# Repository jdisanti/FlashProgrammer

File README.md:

128KiB 17-bit Addressed 32-pin Flash ROM Programmer
---------------------------------------------------

This package includes the schematic, PCB design, and software for an USB
Flash Programmer to read/write the contents of 128KiB 32-pin Flash ROM chips,
such as the GLS27SF010 by Greenliant.

This is my second electronics project, and a stepping stone to building my
own 8-bit computer. I made a lot of mistakes along the way and learned a ton.
After four PCB revisions, and hours of frustrating debugging, I finally got it
to successfully erase, write, and verify the contents of a ROM.

## Demo

## Project Structure

The `avr/` directory contains all of the software to be run on the Atmel
ATMEGA328 chip on the board. This needs to be compiled and programmed onto
the board using an ISP on the ISP headers.

The `design/` directory contains the schematic and PCB design in the original
KiCad file formats. The BOM file is also here.

The `PDFs/` directory contains PDF output for the schematic and PCB.

The `software/` directory contains the software that runs on the PC to
communicate with the device over USB serial. It's written in Rust and can
be compiled/run on Linux, Mac, and Windows without a hitch.

Finally, `symbol_generation/` contains some CSV files used to generate
schematic symbols with KiPart.

## What I Learned

This project presented a lot of firsts for me. My previous project, a binary
clock, had taught me how to design a digital circuit with a microcontroller,
draw schematics, and create PCBs.

This project, above all other things, taught me patience. If you read the
next section about the mistakes I made, you'll see why. I learned that I
really need to slow down, be sure to read all of the datasheets, double
check my schematics and footprints, and cross-check my schematic against
the datasheets. Then after all of that, wait a week and then do it again.

Coming from a software background made this a very hard lesson. I'm used to
making small incremental changes and getting test results immediately. Working
in an area where incremental changes are expensive, and where testing is
time-consuming, requires a difficult change of mindset.

Something I didn't do with this project was breadboarding. I wanted to see
if I could design and build a working circuit without that step. I've learned
that I can play around with little "mock" circuits in LTSpice to test some
of my assumptions, and then also build those out on breadboard without having
to build the entire circuit. This was useful for designing the A9 signal/12V
switching circuit.

## Mistakes I Made

Since the goal of this project was to learn, I've decided to document all
the mistakes I made for future reference.

**First board (not in version control)**
- I didn't read the entire datasheet for the MAX662A, and thus, didn't realize
  I needed capacitors on the 12V output. This led to there being no 12V supply
  on that board.
- I tried to be clever and soldered the board up in sections so I could test each
  individually. This is how I discovered the 12V supply wasn't working, but I didn't
  continue testing the other sections after that discovery, and thus, didn't
  discover my next mistake until the next board.

**Second board**
- I got the pins on the SOT-23 2N3906 transistor wrong, and lost a decent
  chunk of time debugging that, and then soldering it on upside-down to fix it.
- I discovered that I couldn't use the daisy chaining pin on the 74HC595
  as the 17th bit of the address. I should have looked at the timing diagram
  in the datasheet to verify my assumption. I was actually able to bodge this
  by severing the A16 line and wiring it to the three unused pins on the micro
  (and setting all three pins to the same output since they were tied together).
- I used the ISP pins for both programming the MCU and talking to the ROM chip,
  but I neglected to add resistors so that I could program the MCU while the
  ROM chip was populated on the board. Unfortunately, I didn't realize this at
  the time, and thought I had fried my MCU somehow. Since I had already discovered
  the address line mistake, I just built another revision instead of doing
  more testing (I didn't have a rework station at the time and didn't want to
  solder another board either).

**Third board**
- I discovered that erasing didn't work because I failed to realize that
  the 12V had to be applied to both the VPP and A9 pins during the erase process.

**Fourth board**
- I didn't put a pull-down resistor on the A9 signal after the diodes. This
  forced me to add a hefty delay loop of 160uS in the code that set the address.
  This mistake is still present in the design since it wasn't fatal.

## License

All of the contents of this package are licensed under the Solderpad 0.51
license. Please read the LICENSE.md included for more details.

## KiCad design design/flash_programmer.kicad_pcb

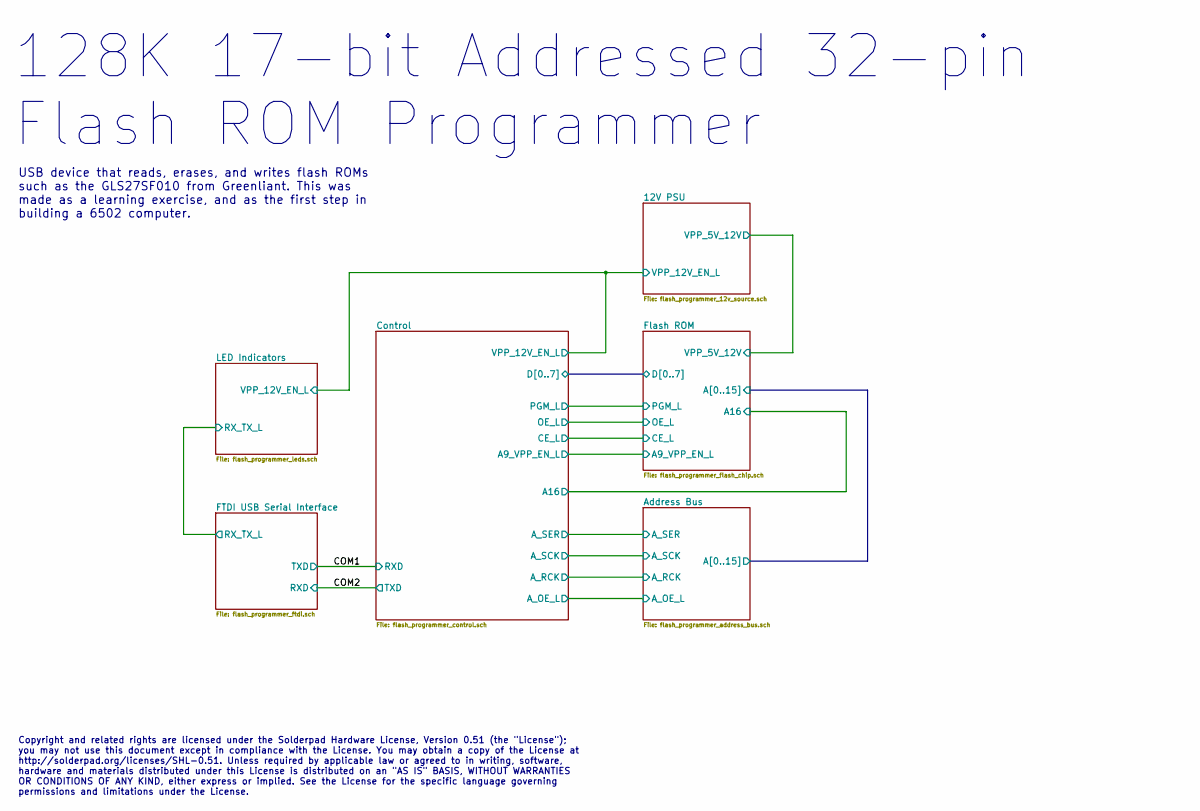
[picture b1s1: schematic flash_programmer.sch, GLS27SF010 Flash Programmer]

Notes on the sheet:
128K 17-bit Addressed 32-pin Flash ROM Programmer
USB device that reads, erases, and writes flash ROMs such as the GLS27SF010 from Greenliant. This was made as a learning exercise, and as the first step in building a 6502 computer.
Copyright and related rights are licensed under the Solderpad Hardware License, Version 0.51 (the "License"); you may not use this document except in compliance with the License. You may obtain a copy of the License at http://solderpad.org/licenses/SHL-0.51. Unless required by applicable law or agr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

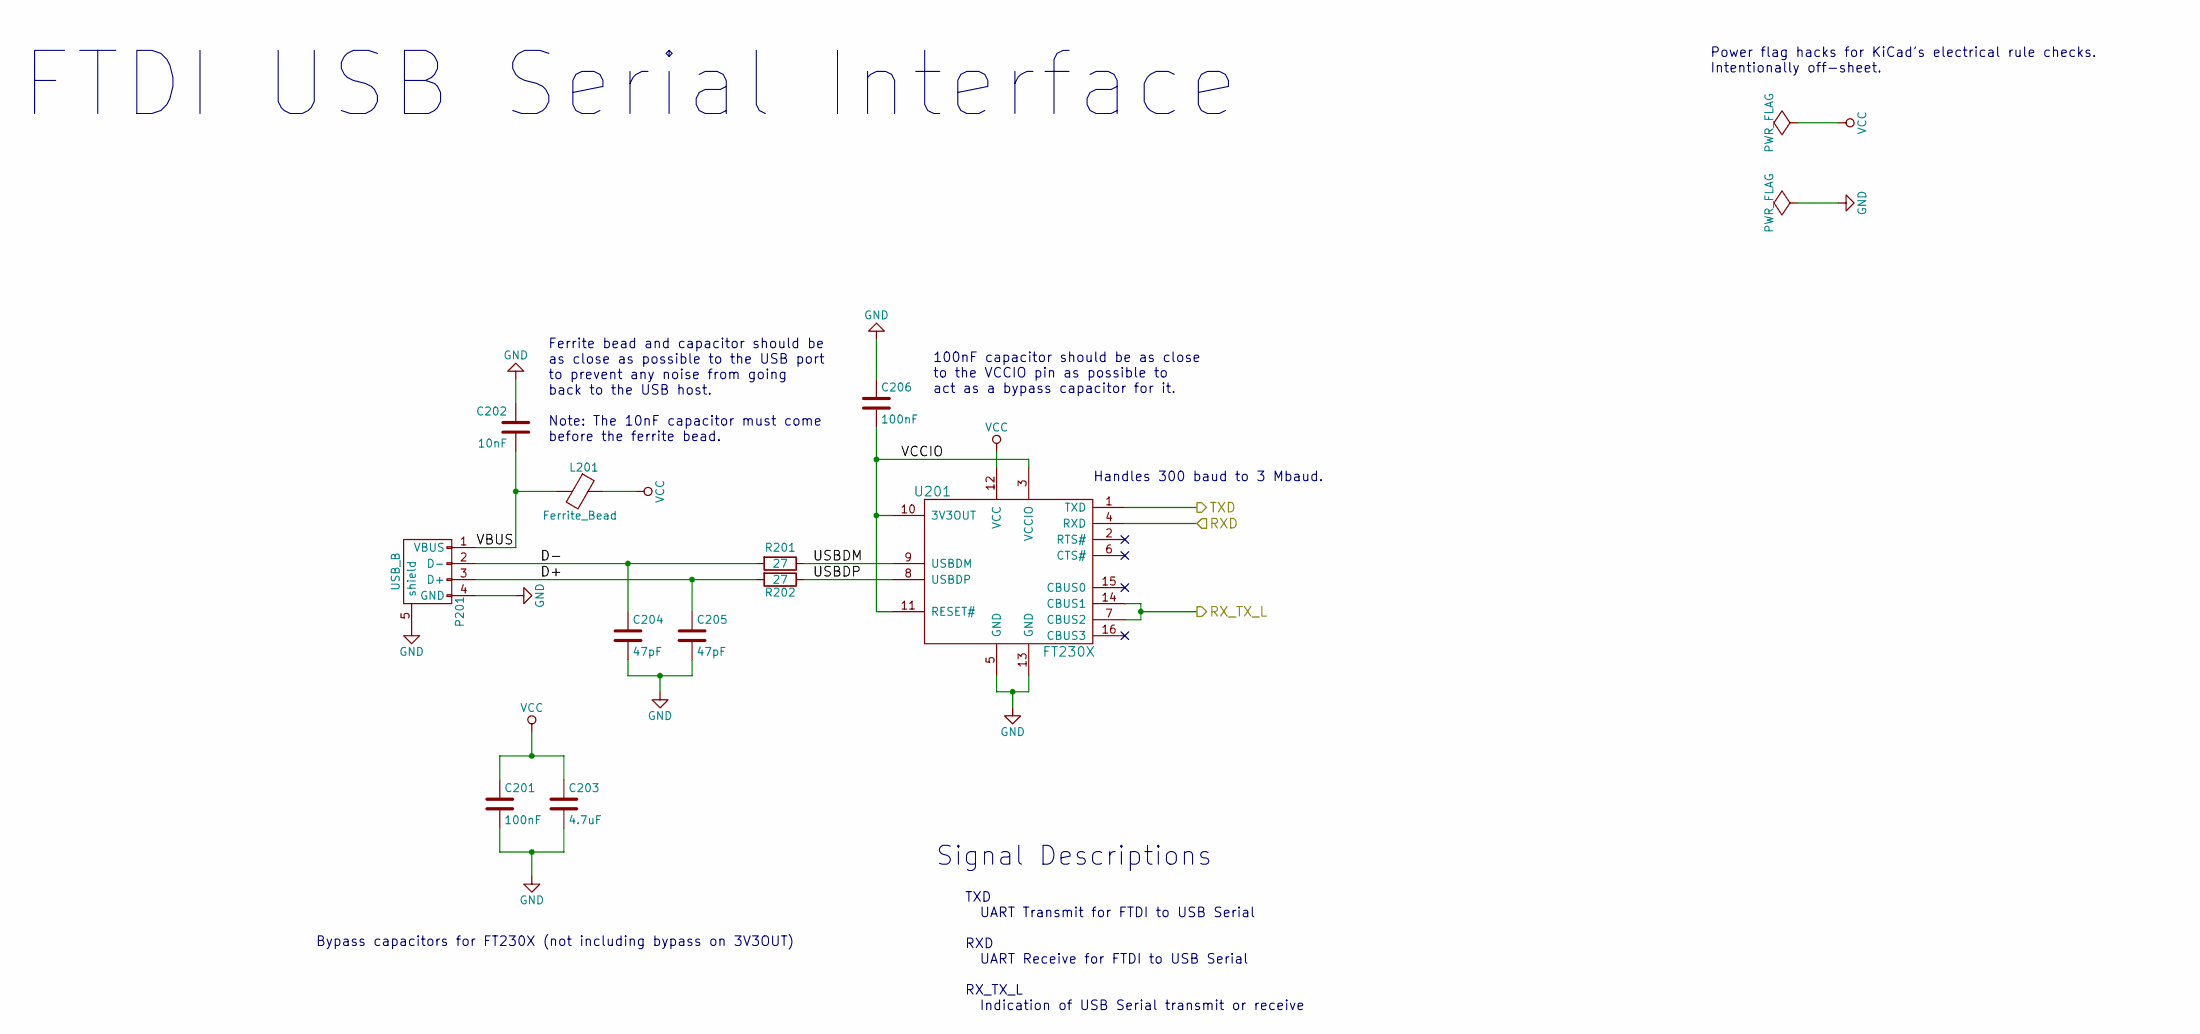
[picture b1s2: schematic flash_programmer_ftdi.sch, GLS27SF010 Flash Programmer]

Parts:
C201, C206: 100nF; R_0603_HandSoldering
C202: 10nF; R_0603_HandSoldering
C203: 4.7uF; R_0805_HandSoldering
C204, C205: 47pF; R_0603_HandSoldering
L201: Ferrite_Bead; R_0805_HandSoldering
P201: USB_B
R201, R202: 27; R_0603_HandSoldering
U201: FT230X; SSOP-16

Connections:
/COM1: U201.1 (TXD); also elsewhere on the board
/COM2: U201.4 (RXD); also elsewhere on the board
/FTDI USB Serial Interface/D+: C205.1, P201.3 (D+), R202.2
/FTDI USB Serial Interface/D-: C204.1, P201.2 (D-), R201.2
/FTDI USB Serial Interface/RX_TX_L: U201.7 (CBUS2), U201.14 (CBUS1); also elsewhere on the board
/FTDI USB Serial Interface/USBDM: R201.1, U201.9 (USBDM)
/FTDI USB Serial Interface/USBDP: R202.1, U201.8 (USBDP)
/FTDI USB Serial Interface/VBUS: C202.1, L201.2, P201.1 (VBUS)
/FTDI USB Serial Interface/VCCIO: C206.2, U201.3 (VCCIO), U201.10 (3V3OUT), U201.11 (RESET#)
GND: C201.2, C202.2, C203.2, C204.2, C205.2, C206.1, P201.4 (GND), P201.5 (shield), U201.5 (GND), U201.13 (GND); also elsewhere on the board
VCC: C201.1, C203.1, L201.1, U201.12 (VCC); also elsewhere on the board

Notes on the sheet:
Bypass capacitors for FT230X (not including bypass on 3V3OUT)
Ferrite bead and capacitor should be as close as possible to the USB port to prevent any noise from going back to the USB host. Note: The 10nF capacitor must come before the ferrite bead.
100nF capacitor should be as close to the VCCIO pin as possible to act as a bypass capacitor for it.
Power flag hacks for KiCad's electrical rule checks. Intentionally off-sheet.
FTDI USB Serial Interface
Signal Descriptions
TXD UART Transmit for FTDI to USB Serial RXD UART Receive for FTDI to USB Serial RX_TX_L Indication of USB Serial transmit or receive
Handles 300 baud to 3 Mbaud.

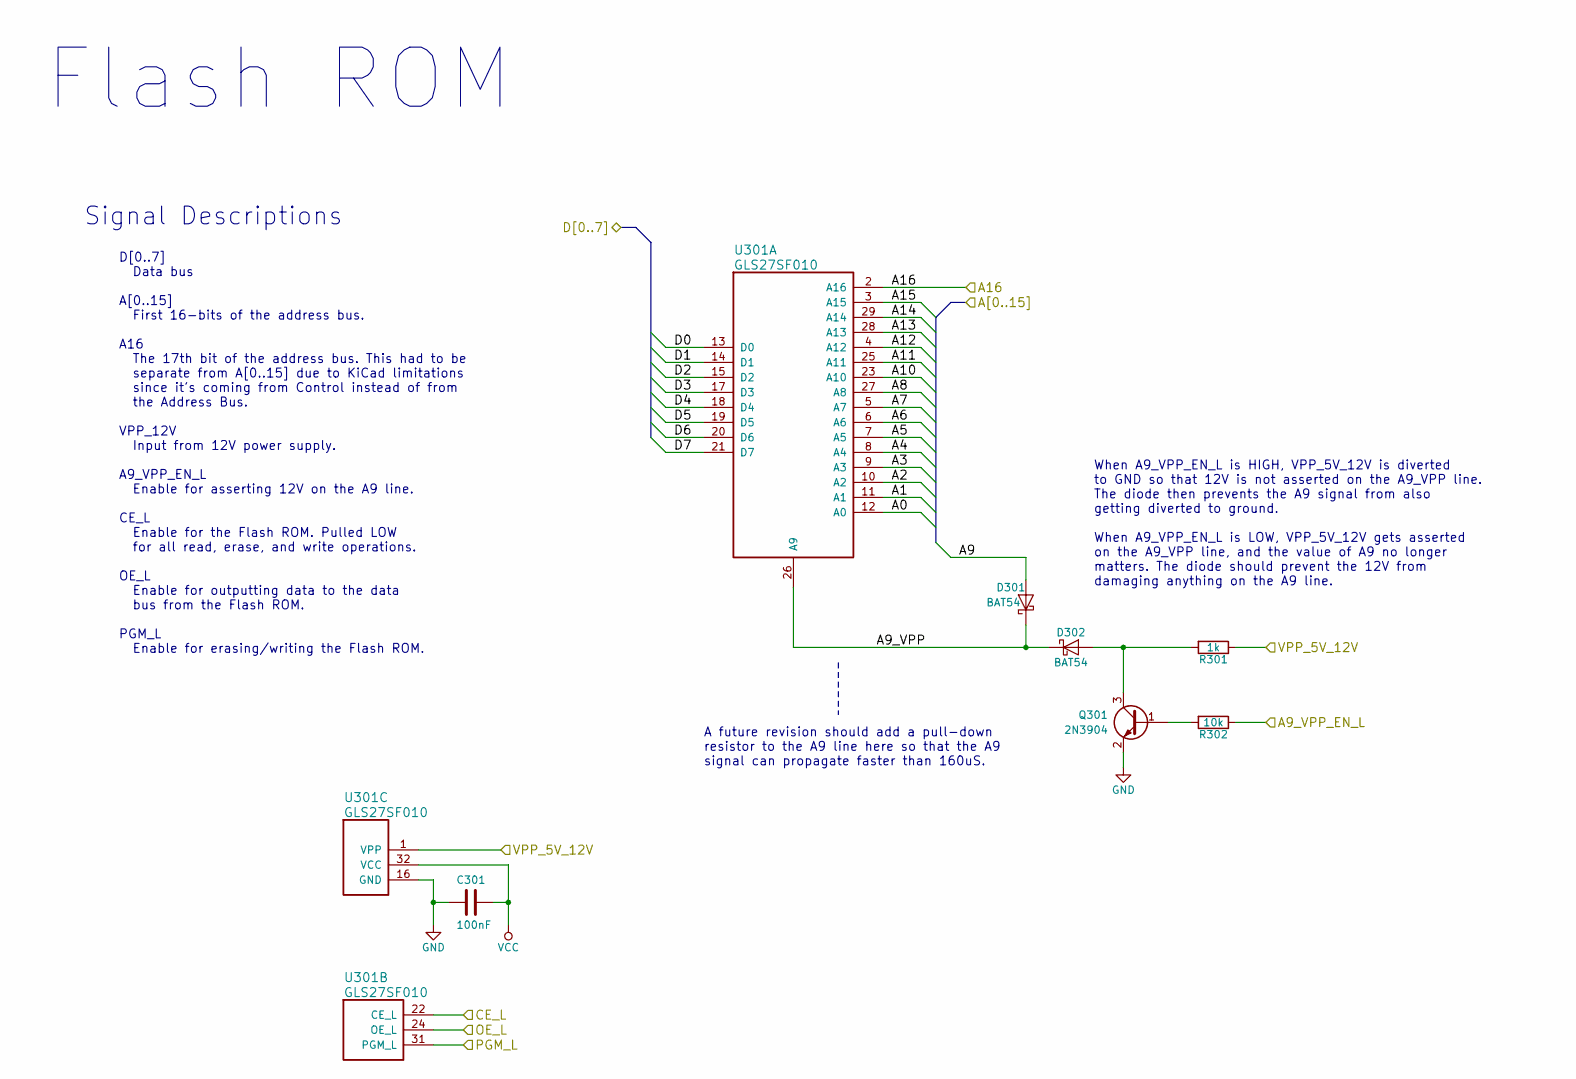
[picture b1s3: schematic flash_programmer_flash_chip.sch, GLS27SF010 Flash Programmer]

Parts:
C301: 100nF; R_0603_HandSoldering
D301, D302: BAT54; D_SOT-23_ANK
Q301: 2N3904; SOT-23_Handsoldering
R301: 1k; R_0603_HandSoldering
R302: 10k; R_0603_HandSoldering
U301: GLS27SF010; DIP-32_W15.24mm

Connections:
/12V PSU/VPP_5V_12V: R301.1, U301.1 (VPP); also elsewhere on the board
/Address Bus/A0: U301.12 (A0); also elsewhere on the board
/Address Bus/A1: U301.11 (A1); also elsewhere on the board
/Address Bus/A2: U301.10 (A2); also elsewhere on the board
/Address Bus/A3: U301.9 (A3); also elsewhere on the board
/Address Bus/A4: U301.8 (A4); also elsewhere on the board
/Address Bus/A5: U301.7 (A5); also elsewhere on the board
/Address Bus/A6: U301.6 (A6); also elsewhere on the board
/Address Bus/A7: U301.5 (A7); also elsewhere on the board
/Address Bus/A8: U301.27 (A8); also elsewhere on the board
/Address Bus/A9: D301.2 (A); also elsewhere on the board
/Address Bus/A10: U301.23 (A10); also elsewhere on the board
/Address Bus/A11: U301.25 (A11); also elsewhere on the board
/Address Bus/A12: U301.4 (A12); also elsewhere on the board
/Address Bus/A13: U301.28 (A13); also elsewhere on the board
/Address Bus/A14: U301.29 (A14); also elsewhere on the board
/Address Bus/A15: U301.3 (A15); also elsewhere on the board
/Control/A9_VPP_EN_L: R302.1; also elsewhere on the board
/Control/A16: U301.2 (A16); also elsewhere on the board
/Control/CE_L: U301.22 (CE_L); also elsewhere on the board
/Control/D0: U301.13 (D0); also elsewhere on the board
/Control/D1: U301.14 (D1); also elsewhere on the board
/Control/D2: U301.15 (D2); also elsewhere on the board
/Control/D3: U301.17 (D3); also elsewhere on the board
/Control/D4: U301.18 (D4); also elsewhere on the board
/Control/D5: U301.19 (D5); also elsewhere on the board
/Control/D6: U301.20 (D6); also elsewhere on the board
/Control/D7: U301.21 (D7); also elsewhere on the board
/Control/OE_L: U301.24 (OE_L); also elsewhere on the board
/Control/PGM_L: U301.31 (PGM_L); also elsewhere on the board
/Flash ROM/A9_VPP: D301.1 (K), D302.1 (K), U301.26 (A9)
GND: C301.2, Q301.2 (E), U301.16 (GND); also elsewhere on the board
unnamed: D302.2 (A), Q301.3 (C), R301.2
unnamed: Q301.1 (B), R302.2
VCC: C301.1, U301.32 (VCC); also elsewhere on the board

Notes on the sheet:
Flash ROM
When A9_VPP_EN_L is HIGH, VPP_5V_12V is diverted to GND so that 12V is not asserted on the A9_VPP line. The diode then prevents the A9 signal from also getting diverted to ground. When A9_VPP_EN_L is LOW, VPP_5V_12V gets asserted on the A9_VPP line, and the value of A9 no longer matters. The diode 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
D[0..7] Data bus A[0..15] First 16-bits of the address bus. A16 The 17th bit of the address bus. This had to be separate from A[0..15] due to KiCad limitations since it's coming from Control instead of from the Address Bus. VPP_12V Input from 12V power supply. A9_VPP_EN_L Enable for asserting 12V o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
Signal Descriptions
A future revision should add a pull-down resistor to the A9 line here so that the A9 signal can propagate faster than 160uS.

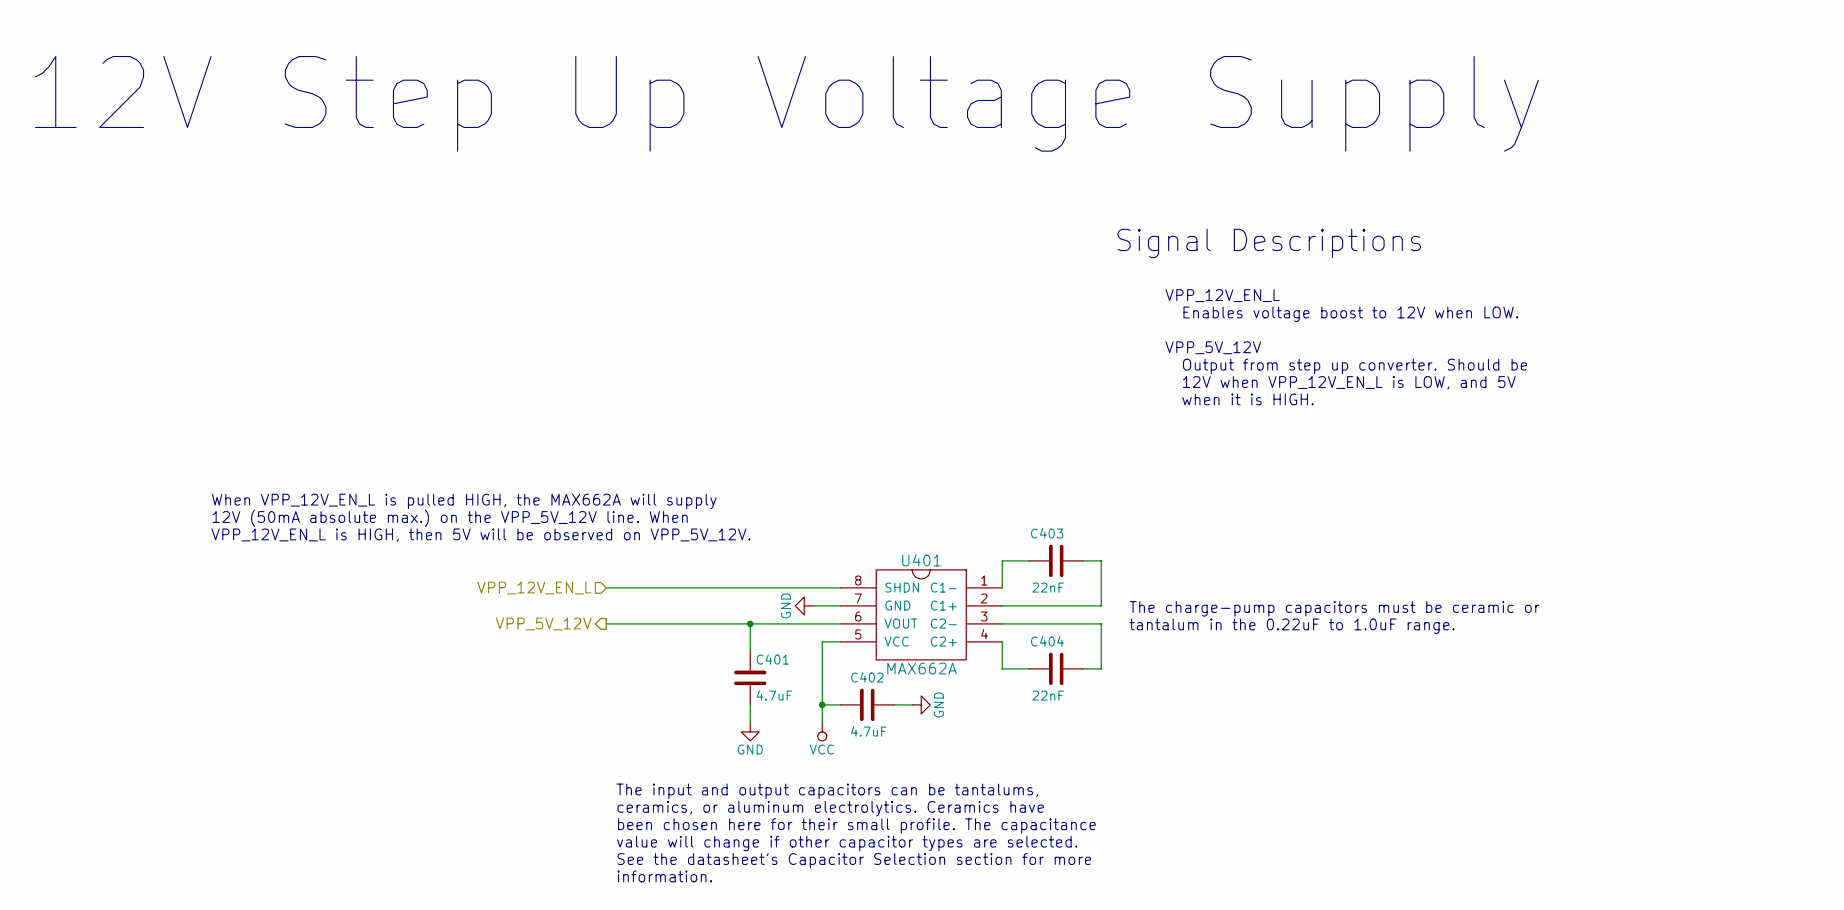
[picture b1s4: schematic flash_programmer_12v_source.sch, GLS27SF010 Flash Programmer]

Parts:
C401, C402: 4.7uF; R_0805_HandSoldering
C403, C404: 22nF; R_0603_HandSoldering
U401: MAX662A; SOIC-8_3.9x4.9mm_Pitch1.27mm

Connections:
/12V PSU/VPP_5V_12V: C401.1, U401.6 (VOUT); also elsewhere on the board
/12V PSU/VPP_12V_EN_L: U401.8 (SHDN); also elsewhere on the board
GND: C401.2, C402.1, U401.7 (GND); also elsewhere on the board
unnamed: C403.1, U401.1 (C1-)
unnamed: C403.2, U401.2 (C1+)
unnamed: C404.1, U401.4 (C2+)
unnamed: C404.2, U401.3 (C2-)
VCC: C402.2, U401.5 (VCC); also elsewhere on the board

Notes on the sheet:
12V Step Up Voltage Supply
When VPP_12V_EN_L is pulled HIGH, the MAX662A will supply 12V (50mA absolute max.) on the VPP_5V_12V line. When VPP_12V_EN_L is HIGH, then 5V will be observed on VPP_5V_12V.
The charge-pump capacitors must be ceramic or tantalum in the 0.22uF to 1.0uF range.
The input and output capacitors can be tantalums, ceramics, or aluminum electrolytics. Ceramics have been chosen here for their small profile. The capacitance value will change if other capacitor types are selected. See the datasheet's Capacitor Selection section for more information.
Signal Descriptions
VPP_12V_EN_L Enables voltage boost to 12V when LOW. VPP_5V_12V Output from step up converter. Should be 12V when VPP_12V_EN_L is LOW, and 5V when it is HIGH.

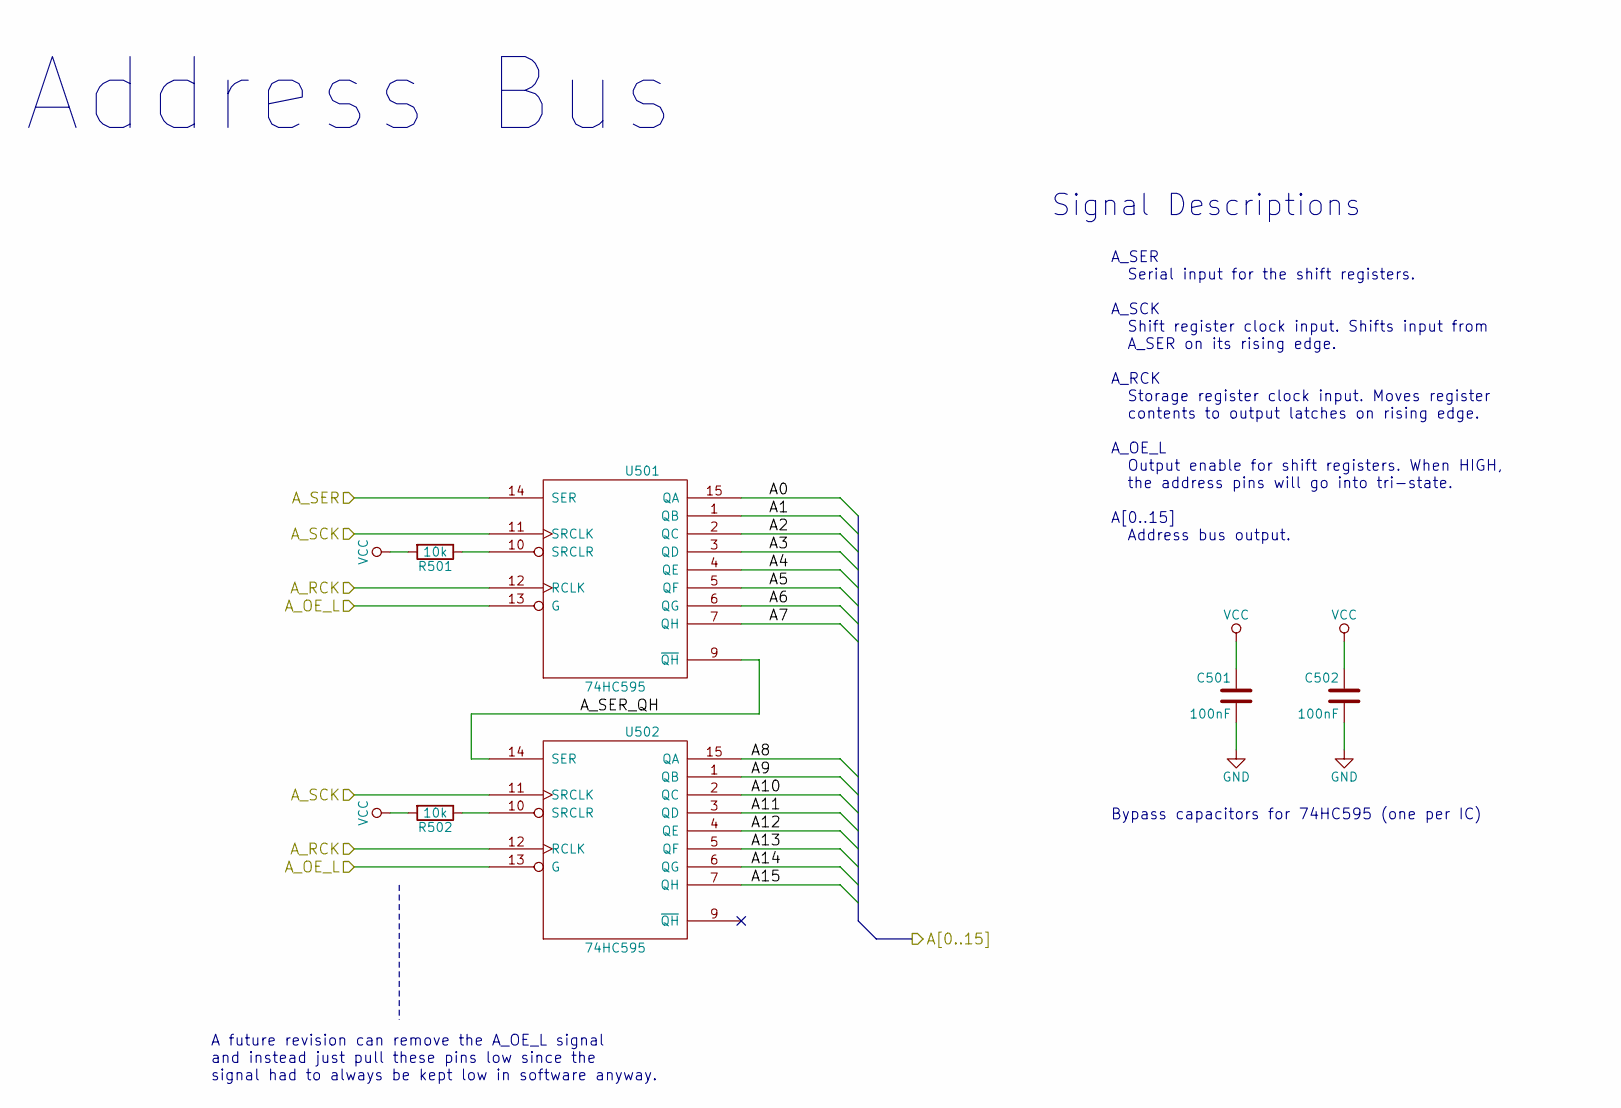
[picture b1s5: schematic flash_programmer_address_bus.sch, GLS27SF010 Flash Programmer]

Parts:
C501, C502: 100nF; R_0603_HandSoldering
R501, R502: 10k; R_0603_HandSoldering
U501, U502: 74HC595; SOIC-16_3.9x9.9mm_Pitch1.27mm

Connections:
/Address Bus/A0: U501.15 (QA); also elsewhere on the board
/Address Bus/A1: U501.1 (QB); also elsewhere on the board
/Address Bus/A2: U501.2 (QC); also elsewhere on the board
/Address Bus/A3: U501.3 (QD); also elsewhere on the board
/Address Bus/A4: U501.4 (QE); also elsewhere on the board
/Address Bus/A5: U501.5 (QF); also elsewhere on the board
/Address Bus/A6: U501.6 (QG); also elsewhere on the board
/Address Bus/A7: U501.7 (QH); also elsewhere on the board
/Address Bus/A8: U502.15 (QA); also elsewhere on the board
/Address Bus/A9: U502.1 (QB); also elsewhere on the board
/Address Bus/A10: U502.2 (QC); also elsewhere on the board
/Address Bus/A11: U502.3 (QD); also elsewhere on the board
/Address Bus/A12: U502.4 (QE); also elsewhere on the board
/Address Bus/A13: U502.5 (QF); also elsewhere on the board
/Address Bus/A14: U502.6 (QG); also elsewhere on the board
/Address Bus/A15: U502.7 (QH); also elsewhere on the board
/Address Bus/A_OE_L: U501.13 (G), U502.13 (G); also elsewhere on the board
/Address Bus/A_RCK: U501.12 (RCLK), U502.12 (RCLK); also elsewhere on the board
/Address Bus/A_SCK: U501.11 (SRCLK), U502.11 (SRCLK); also elsewhere on the board
/Address Bus/A_SER: U501.14 (SER); also elsewhere on the board
/Address Bus/A_SER_QH: U501.9 (~QH), U502.14 (SER)
GND: C501.2, C502.2, U501.8 (GND), U502.8 (GND); also elsewhere on the board
unnamed: R501.1, U501.10 (SRCLR)
unnamed: R502.1, U502.10 (SRCLR)
VCC: C501.1, C502.1, R501.2, R502.2, U501.16 (VCC), U502.16 (VCC); also elsewhere on the board

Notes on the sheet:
Address Bus
Bypass capacitors for 74HC595 (one per IC)
A_SER Serial input for the shift registers. A_SCK Shift register clock input. Shifts input from A_SER on its rising edge. A_RCK Storage register clock input. Moves register contents to output latches on rising edge. A_OE_L Output enable for shift registers. When HIGH, the address pins will go into 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
Signal Descriptions
A future revision can remove the A_OE_L signal and instead just pull these pins low since the signal had to always be kept low in software anyway.

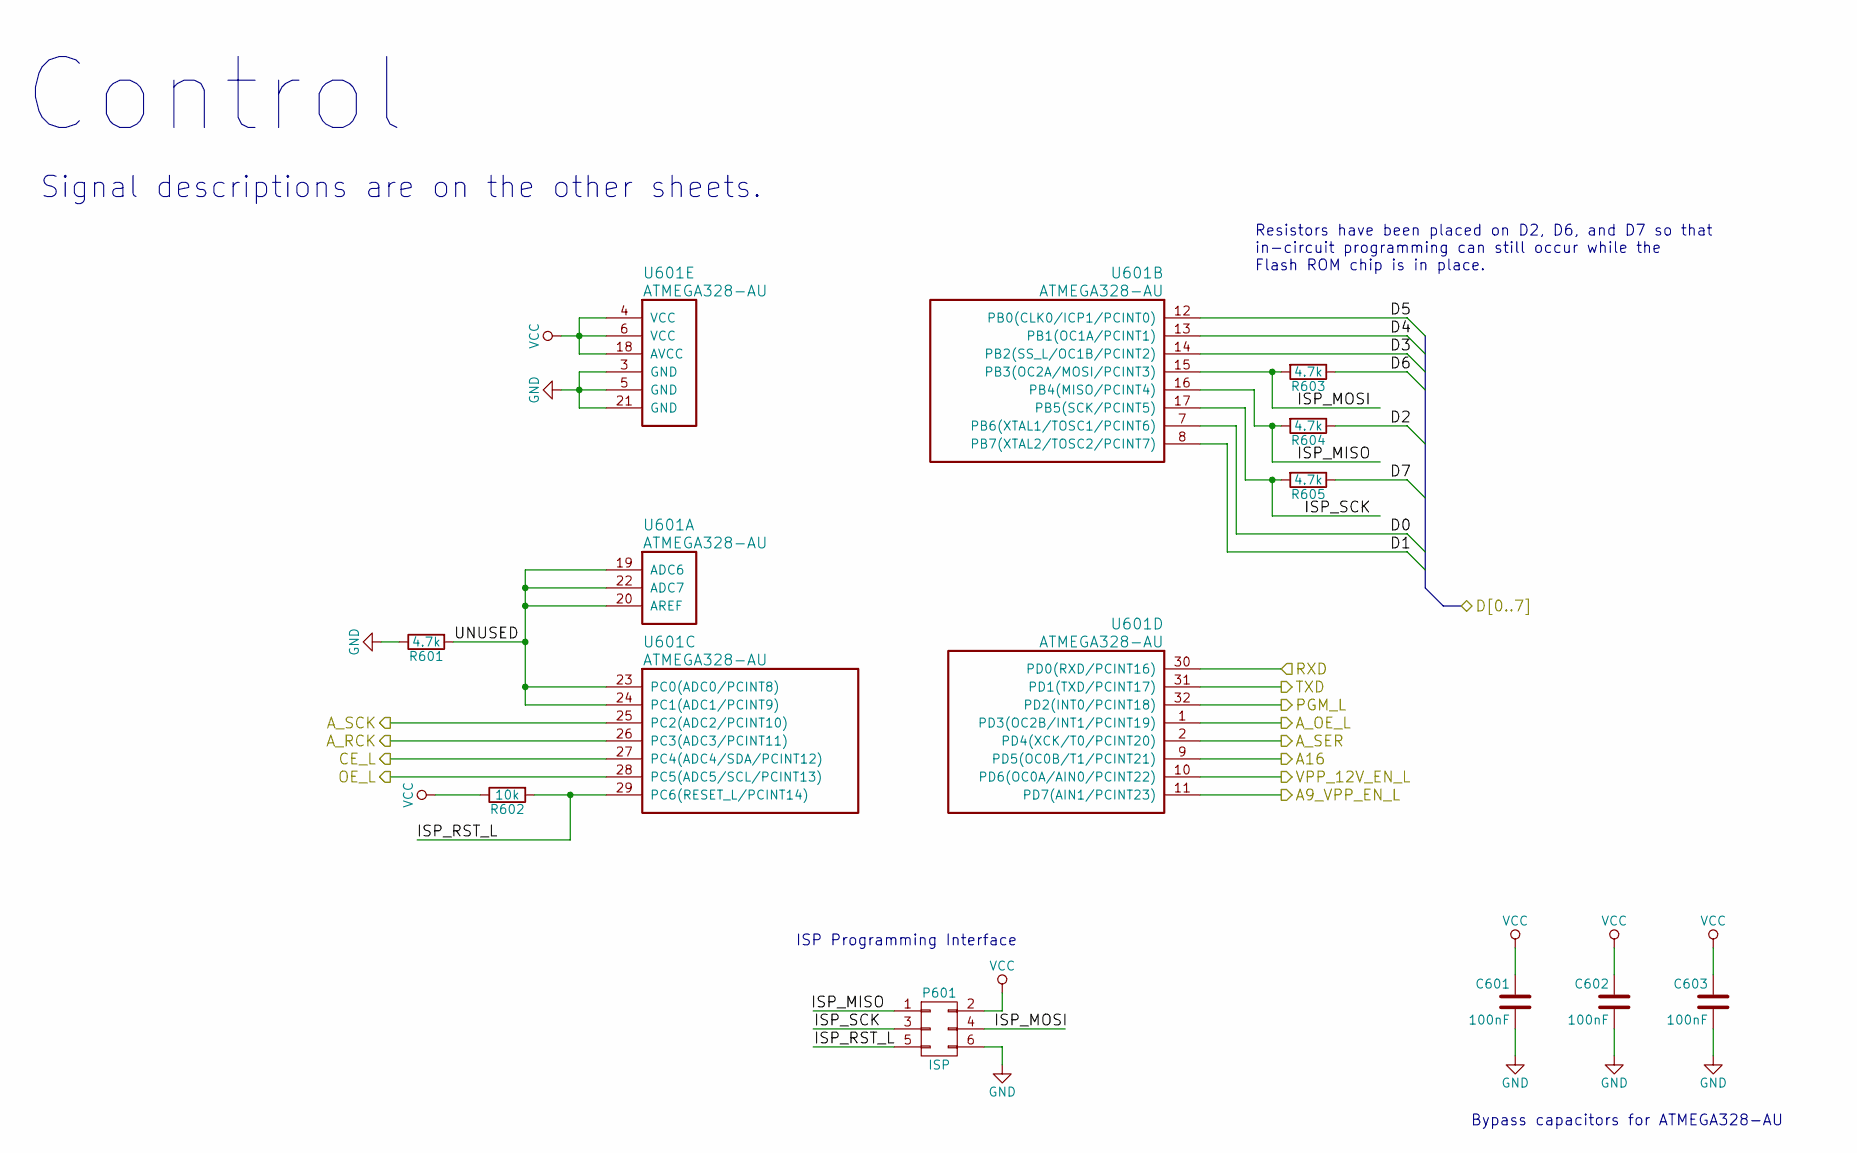
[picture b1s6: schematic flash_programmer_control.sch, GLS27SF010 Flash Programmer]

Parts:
C601, C602, C603: 100nF; R_0603_HandSoldering
P601: ISP; Pin_Header_Straight_2x03_Pitch2.54mm
R601, R603, R604, R605: 4.7k; R_0603_HandSoldering
R602: 10k; R_0603_HandSoldering
U601: ATMEGA328-AU; TQFP-32

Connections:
/12V PSU/VPP_12V_EN_L: U601.10 (PD6(OC0A/AIN0/PCINT22)); also elsewhere on the board
/Address Bus/A_OE_L: U601.1 (PD3(OC2B/INT1/PCINT19)); also elsewhere on the board
/Address Bus/A_RCK: U601.26 (PC3(ADC3/PCINT11)); also elsewhere on the board
/Address Bus/A_SCK: U601.25 (PC2(ADC2/PCINT10)); also elsewhere on the board
/Address Bus/A_SER: U601.2 (PD4(XCK/T0/PCINT20)); also elsewhere on the board
/COM1: U601.30 (PD0(RXD/PCINT16)); also elsewhere on the board
/COM2: U601.31 (PD1(TXD/PCINT17)); also elsewhere on the board
/Control/A9_VPP_EN_L: U601.11 (PD7(AIN1/PCINT23)); also elsewhere on the board
/Control/A16: U601.9 (PD5(OC0B/T1/PCINT21)); also elsewhere on the board
/Control/CE_L: U601.27 (PC4(ADC4/SDA/PCINT12)); also elsewhere on the board
/Control/D0: U601.7 (PB6(XTAL1/TOSC1/PCINT6)); also elsewhere on the board
/Control/D1: U601.8 (PB7(XTAL2/TOSC2/PCINT7)); also elsewhere on the board
/Control/D2: R604.1; also elsewhere on the board
/Control/D3: U601.14 (PB2(SS_L/OC1B/PCINT2)); also elsewhere on the board
/Control/D4: U601.13 (PB1(OC1A/PCINT1)); also elsewhere on the board
/Control/D5: U601.12 (PB0(CLK0/ICP1/PCINT0)); also elsewhere on the board
/Control/D6: R603.1; also elsewhere on the board
/Control/D7: R605.1; also elsewhere on the board
/Control/ISP_MISO: P601.1, R604.2, U601.16 (PB4(MISO/PCINT4))
/Control/ISP_MOSI: P601.4, R603.2, U601.15 (PB3(OC2A/MOSI/PCINT3))
/Control/ISP_RST_L: P601.5, R602.2, U601.29 (PC6(RESET_L/PCINT14))
/Control/ISP_SCK: P601.3, R605.2, U601.17 (PB5(SCK/PCINT5))
/Control/OE_L: U601.28 (PC5(ADC5/SCL/PCINT13)); also elsewhere on the board
/Control/PGM_L: U601.32 (PD2(INT0/PCINT18)); also elsewhere on the board
/Control/UNUSED: R601.2, U601.19 (ADC6), U601.20 (AREF), U601.22 (ADC7), U601.23 (PC0(ADC0/PCINT8)), U601.24 (PC1(ADC1/PCINT9))
GND: C601.2, C602.2, C603.2, P601.6, R601.1, U601.3 (GND), U601.5 (GND), U601.21 (GND); also elsewhere on the board
VCC: C601.1, C602.1, C603.1, P601.2, R602.1, U601.4 (VCC), U601.6 (VCC), U601.18 (AVCC); also elsewhere on the board

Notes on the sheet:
Bypass capacitors for ATMEGA328-AU
ISP Programming Interface
Control
Signal descriptions are on the other sheets.
Resistors have been placed on D2, D6, and D7 so that in-circuit programming can still occur while the Flash ROM chip is in place.

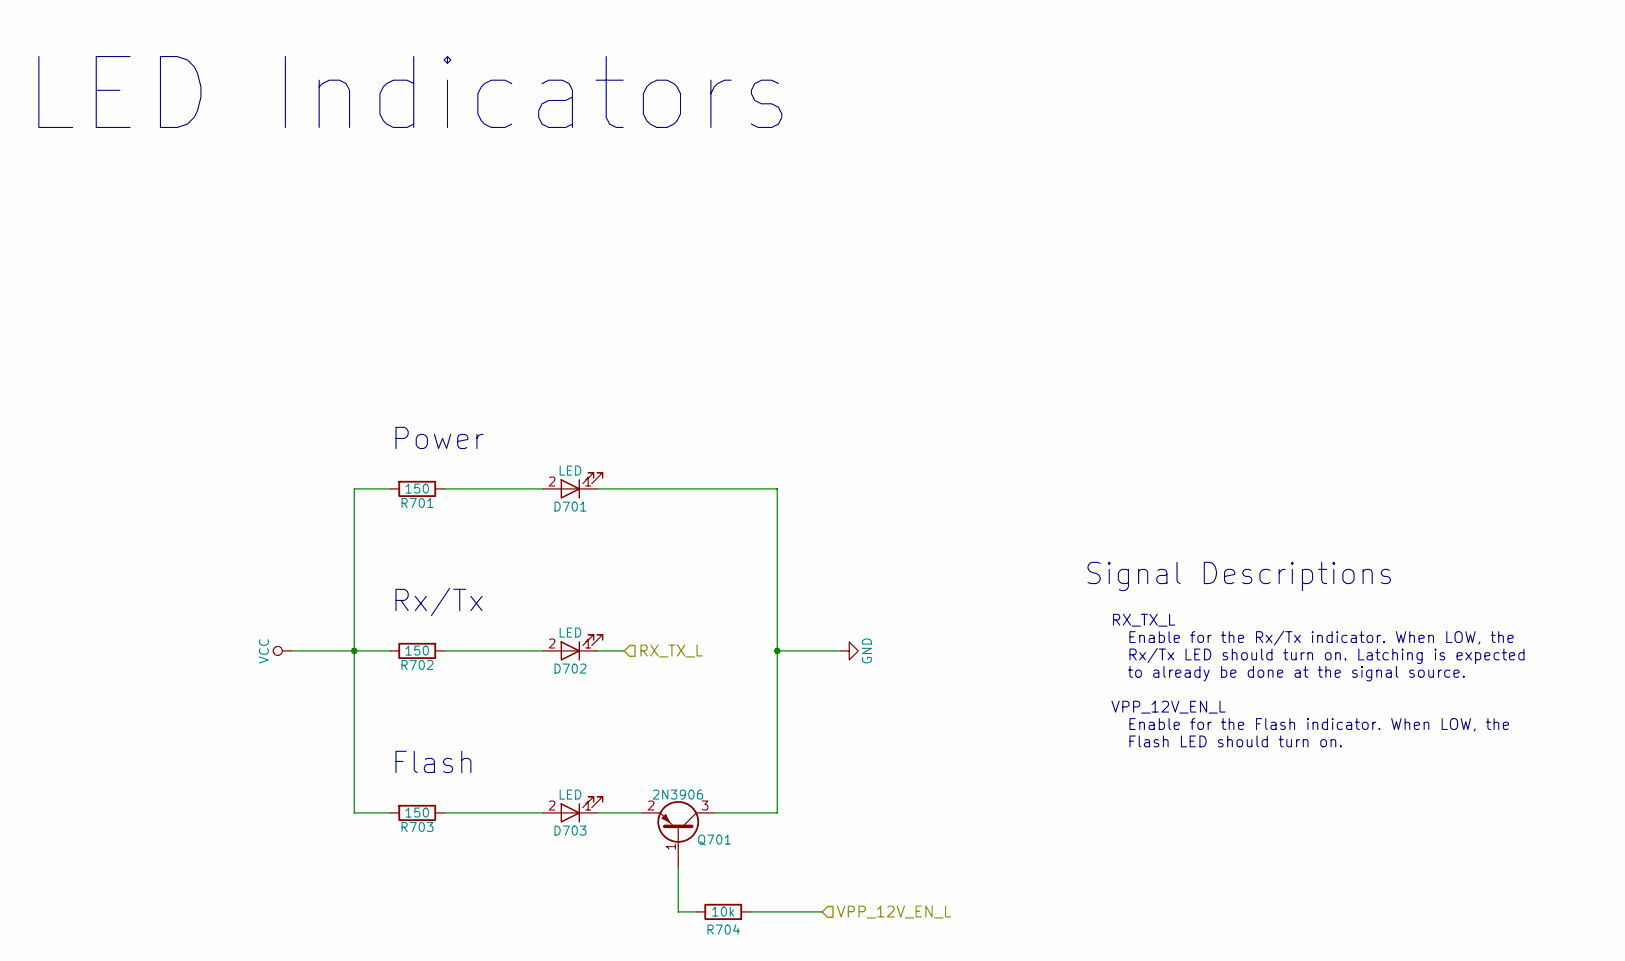
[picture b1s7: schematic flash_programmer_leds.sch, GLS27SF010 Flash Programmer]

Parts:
D701, D702, D703: LED; LED_0805
Q701: 2N3906; SOT-23_Handsoldering
R701, R702, R703: 150; R_0603_HandSoldering
R704: 10k; R_0603_HandSoldering

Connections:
/12V PSU/VPP_12V_EN_L: R704.2; also elsewhere on the board
/FTDI USB Serial Interface/RX_TX_L: D702.1 (K); also elsewhere on the board
GND: D701.1 (K), Q701.3 (C); also elsewhere on the board
unnamed: D701.2 (A), R701.1
unnamed: D702.2 (A), R702.2
unnamed: D703.1 (K), Q701.2 (E)
unnamed: D703.2 (A), R703.1
unnamed: Q701.1 (B), R704.1
VCC: R701.2, R702.1, R703.2; also elsewhere on the board

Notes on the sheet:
Rx/Tx
Power
Flash
LED Indicators
Signal Descriptions
RX_TX_L Enable for the Rx/Tx indicator. When LOW, the Rx/Tx LED should turn on. Latching is expected to already be done at the signal source. VPP_12V_EN_L Enable for the Flash indicator. When LOW, the Flash LED should turn on.

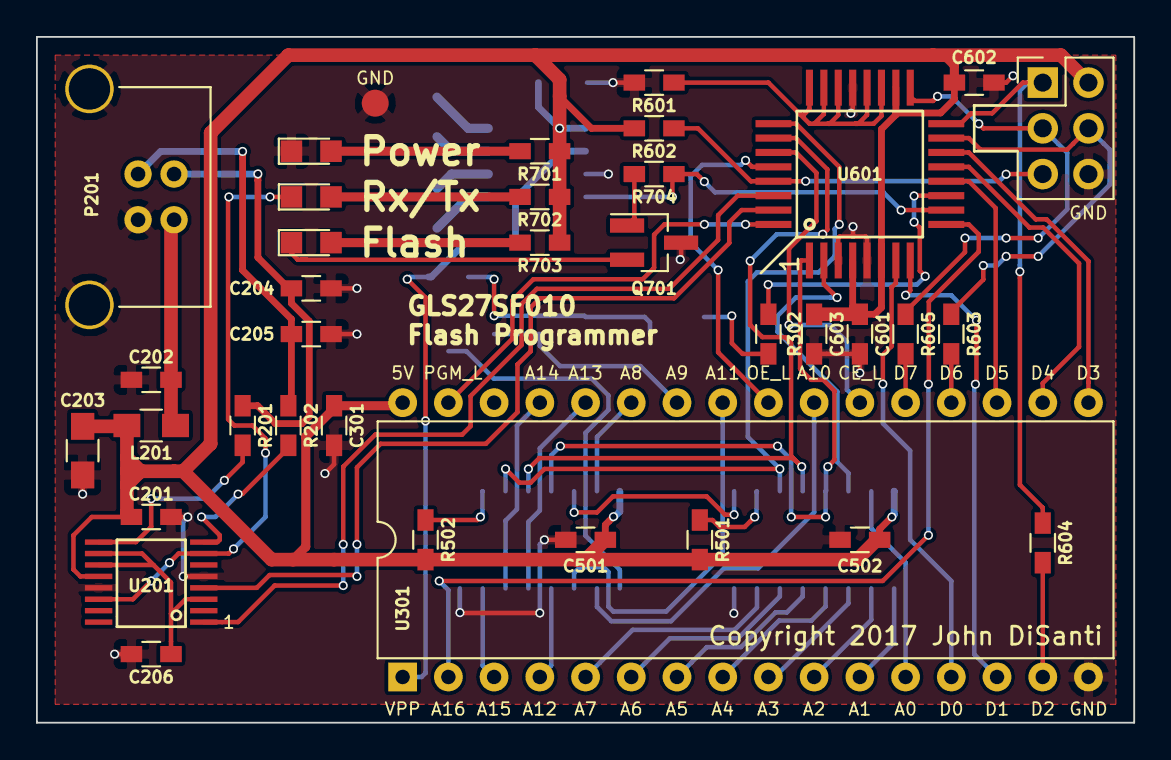
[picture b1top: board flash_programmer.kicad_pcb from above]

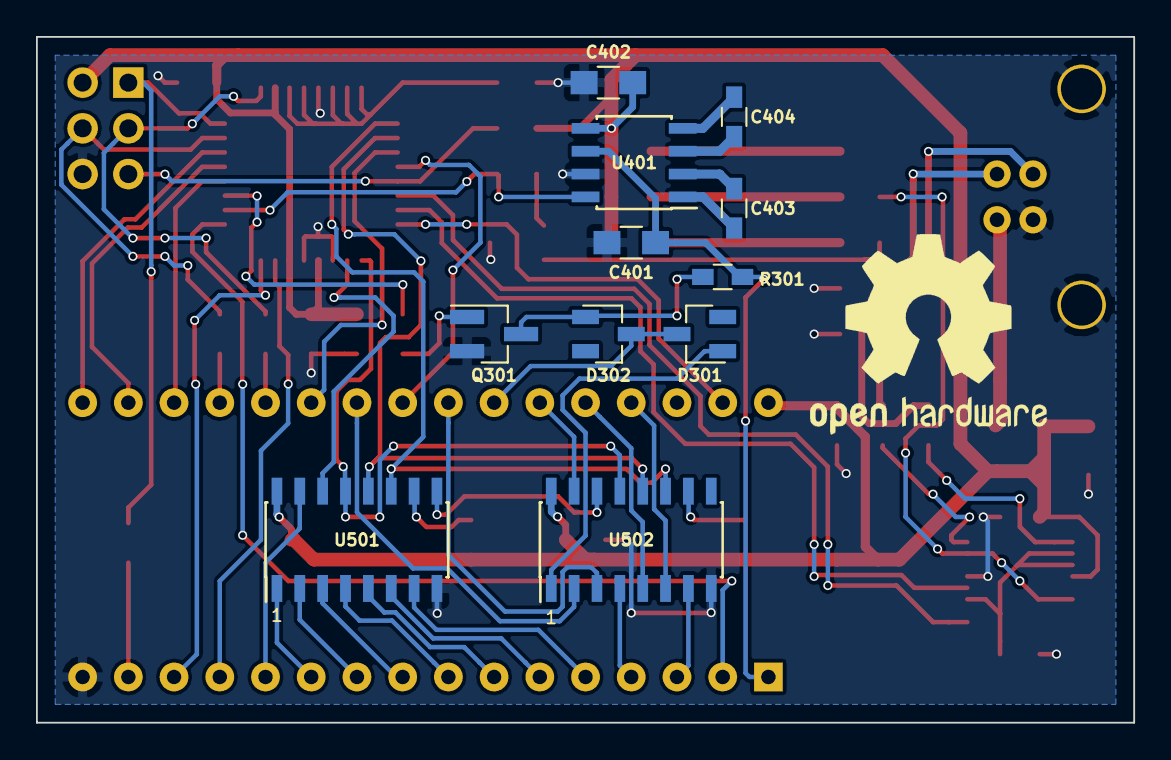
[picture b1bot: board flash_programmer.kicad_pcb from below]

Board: 2 copper layers, 61.0 x 38.1 mm, 48 parts (11 on the bottom side), 66 nets.

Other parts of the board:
GND: Measurement_Point_Round-SMD-Pad_Small

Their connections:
GND: GND.1; also elsewhere on the board

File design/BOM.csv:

Id,Designator,Package,Quantity,Designation,Supplier and ref
1,P601,Pin_Header_Straight_2x03_Pitch2.54mm,1,ISP,
2,P201,USB_B,1,USB_B,
3,Q301,SOT-23_Handsoldering,1,2N3904,
4,"D301,D302",D_SOT-23_ANK,2,BAT54,
5,"C201,C206,C301,C501,C502,C601,C602,C603",R_0603_HandSoldering,8,100nF,
6,C202,R_0603_HandSoldering,1,10nF,
7,"C203,C401,C402",R_0805_HandSoldering,3,4.7uF,
8,"C204,C205",R_0603_HandSoldering,2,47pF,
9,"C403,C404",R_0603_HandSoldering,2,22nF,
10,"D701,D702,D703",LED_0805,3,LED,
11,L201,R_0805_HandSoldering,1,Ferrite_Bead,
12,Q701,SOT-23_Handsoldering,1,2N3906,
13,"R201,R202",R_0603_HandSoldering,2,27,
14,R301,R_0603_HandSoldering,1,1k,
15,"R302,R501,R502,R602,R704",R_0603_HandSoldering,5,10k,
16,"R601,R603,R604,R605",R_0603_HandSoldering,4,4.7k,
17,"R701,R702,R703",R_0603_HandSoldering,3,150,
18,U201,SSOP-16,1,FT230X,
19,U301,DIP-32_W15.24mm,1,GLS27SF010,
20,U401,SOIC-8_3.9x4.9mm_Pitch1.27mm,1,MAX662A,
21,"U501,U502",SOIC-16_3.9x9.9mm_Pitch1.27mm,2,74HC595,
22,U601,TQFP-32,1,ATMEGA328-AU,
